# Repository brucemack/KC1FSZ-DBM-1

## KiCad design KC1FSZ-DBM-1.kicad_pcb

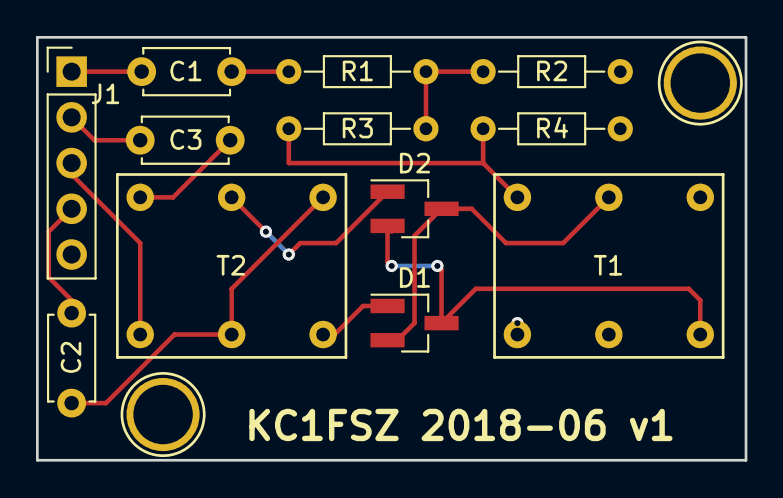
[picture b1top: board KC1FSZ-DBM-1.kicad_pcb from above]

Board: 2 copper layers, 39.4 x 23.5 mm, 12 parts (0 on the bottom side), 14 nets.

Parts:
C1, C2, C3: C; C_Disc_D4.7mm_W2.5mm_P5.00mm
D1, D2: D_Schottky_x2_Serial_CAK; SOT-23_Handsoldering
J1: Conn_01x05; Pin_Header_Straight_1x05_Pitch2.54mm
R1, R2, R3, R4: R; R_Axial_DIN0204_L3.6mm_D1.6mm_P7.62mm_Horizontal
T1, T2: Transformer_1P_2S; TrifilarTransformer_T37_Vertical

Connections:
CLK_IN: C1.2, J1.1
GND: J1.5, R2.2, R4.2, T1.2, T1.4, T1.5
unnamed: C1.1, R1.2
unnamed: C2.1, T2.4, T2.5
unnamed: C3.2, T2.1
unnamed: D1.1, T2.6
unnamed: D1.2, D2.3, T1.3
unnamed: D1.3, D2.2, T1.6
unnamed: D2.1, T2.3
unnamed: R1.1, R2.1, R3.2
unnamed: R3.1, R4.1, T1.1
RF0: C3.1, J1.2
RF0_REF: J1.3, T2.2
RF1: C2.2, J1.4
